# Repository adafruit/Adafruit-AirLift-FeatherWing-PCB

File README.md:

# Adafruit-AirLift-FeatherWing-PCB
PCB files for Adafruit AirLift FeatherWing

Format is EagleCAD schematic and board layout

For more details, check out the product page at

   * https://www.adafruit.com/product/4264

Adafruit invests time and resources providing this open source design, 
please support Adafruit and open-source hardware by purchasing 
products from Adafruit!

Designed by Adafruit Industries.  
Creative Commons Attribution, Share-Alike license, check license.txt for more information
All text above must be included in any redistribution

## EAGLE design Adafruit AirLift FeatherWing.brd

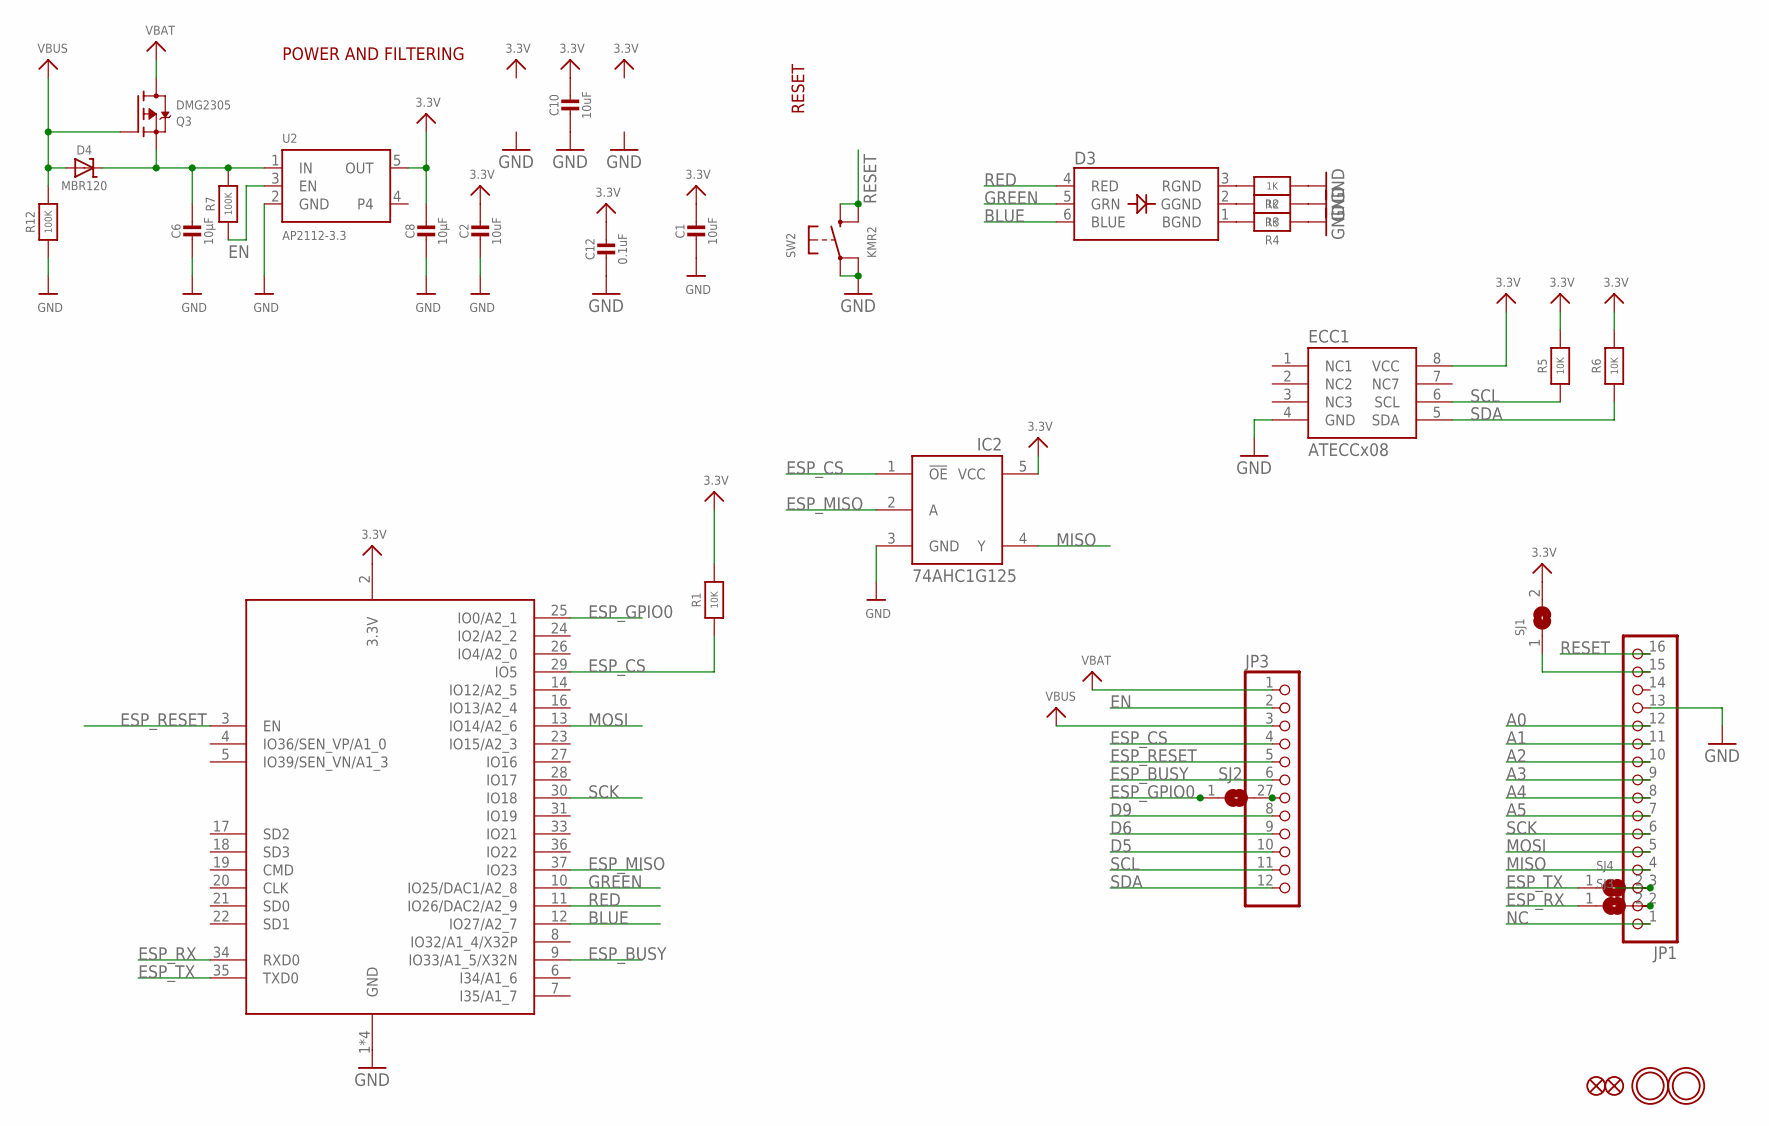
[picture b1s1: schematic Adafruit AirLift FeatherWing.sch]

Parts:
C1, C2, C10: 10uF; 0805-NO
C6, C8: 10µF; 0805-NO
C12: 0.1uF; 0603-NO
D3: LED_RGB_PLCC6CREE-CLV6A; RGBLED_PLCC6
D4: MBR120; SOD-123
ECC1: ATECCx08; SOIC8
IC2: 74AHC1G125; SOT23-5L
JP1: HEADER-1X16_MIN; 1X16_ROUND_MIN
JP3: HEADER-1X12_MIN; 1X12_ROUND_MIN
Q3: DMG2305; SOT23-R
R1, R5, R6: 10K; 0603-NO
R2, R3, R4: 1K; 0603-NO
R7, R12: 100K; 0603-NO
SJ1, SJ2, SJ3, SJ4: SOLDERJUMPER; SOLDERJUMPER_ARROW_NOPASTE
SW2: KMR2; BTN_KMR2_4.6X2.8
U2: AP2112-3.3; SOT23-5
U$31, U$32: MOUNTINGHOLE2.5; MOUNTINGHOLE_2.5_PLATED
U$34, U$35: FIDUCIAL_1MM
X3: ESP32_WROOM32_SKINNY; WROOM32_SKINNY

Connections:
3.3V: C1.1, C2.1, C8.1, C10.1, C12.1, ECC1.8 (VCC), IC2.5 (VCC), R1.2, R5.2, R6.2, SJ1.2, U2.5 (OUT), X3.2 (3.3V)
A0: JP1.12
A1: JP1.11
A2: JP1.10
A3: JP1.9
A4: JP1.8
A5: JP1.7
BLUE: D3.6 (BLUE), X3.12 (IO27/A2_7)
D5: JP3.10
D6: JP3.9
D9: JP3.8
EN: JP3.2, R7.1, U2.3 (EN)
ESP_BUSY: JP3.6, X3.9 (IO33/A1_5/X32N)
ESP_CS: IC2.1 (!OE), JP3.4, R1.1, X3.29 (IO5)
ESP_GPIO0: SJ2.1, X3.25 (IO0/A2_1)
ESP_MISO: IC2.2 (A), X3.37 (IO23)
ESP_RESET: JP3.5, X3.3 (EN)
ESP_RX: SJ3.1, X3.34 (RXD0)
ESP_TX: SJ4.1, X3.35 (TXD0)
GND: C1.2, C2.2, C6.2, C8.2, C10.2, C12.2, ECC1.4 (GND), IC2.3 (GND), JP1.13, R2.1, R3.1, R4.1, R12.1, SW2.A, SW2.A' (P1), U2.2 (GND), X3.1 (GND), X3.15 (GND), X3.38 (GND), X3.P$1 (GND)
GREEN: D3.5 (GRN), X3.10 (IO25/DAC1/A2_8)
MISO: IC2.4 (Y), JP1.4
MOSI: JP1.5, X3.13 (IO14/A2_6)
unnamed: JP1.15, SJ1.1
unnamed: D3.3 (RGND), R2.2
unnamed: D3.2 (GGND), R3.2
unnamed: D3.1 (BGND), R4.2
unnamed: JP3.7, SJ2.2
unnamed: JP1.2, SJ3.2
unnamed: C6.1, D4.C, Q3.2 (S), R7.2, U2.1 (IN)
unnamed: JP1.3, SJ4.2
NC: JP1.1
RED: D3.4 (RED), X3.11 (IO26/DAC2/A2_9)
RESET: JP1.16, SW2.B (S), SW2.B' (S1)
SCK: JP1.6, X3.30 (IO18)
SCL: ECC1.6 (SCL), JP3.11, R5.1
SDA: ECC1.5 (SDA), JP3.12, R6.1
VBAT: JP3.1, Q3.3 (D)
VBUS: D4.A, JP3.3, Q3.1 (G), R12.2

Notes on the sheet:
POWER AND FILTERING
RESET

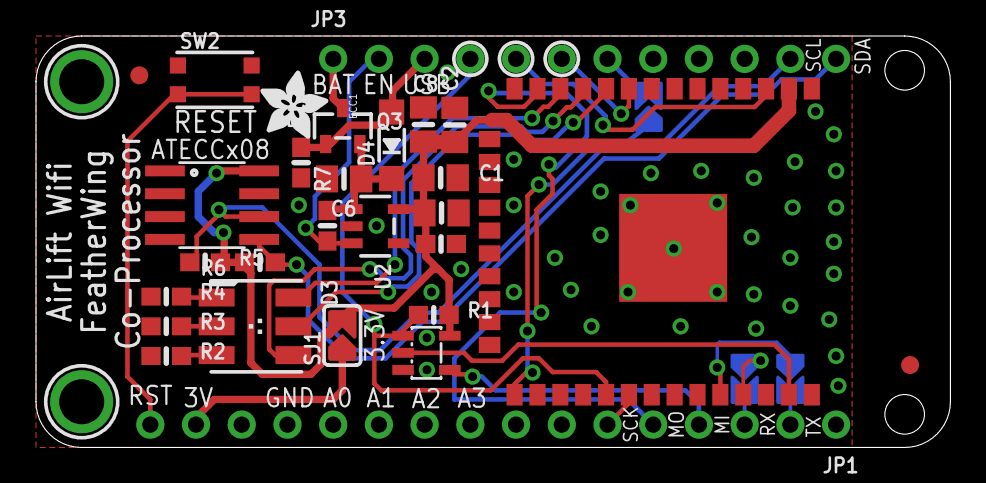
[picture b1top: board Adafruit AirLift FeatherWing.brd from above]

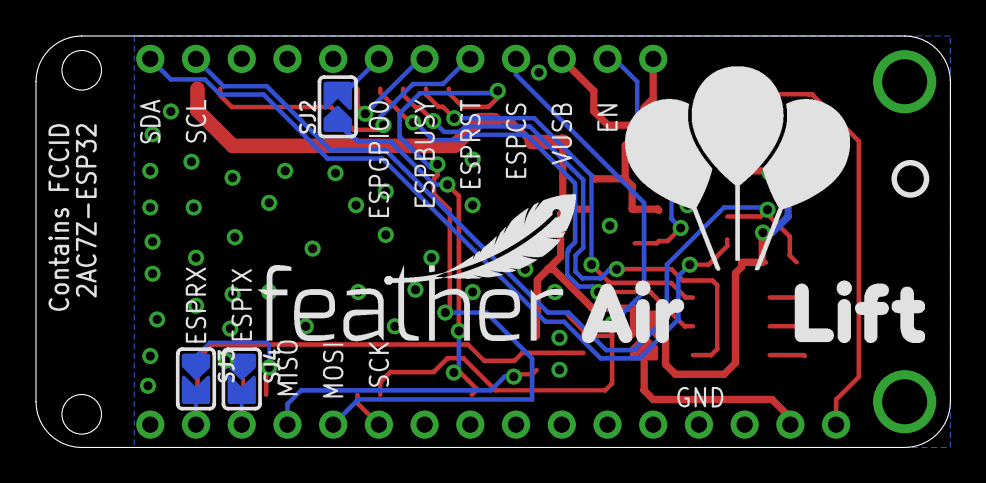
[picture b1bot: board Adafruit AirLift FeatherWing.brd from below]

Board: 2 copper layers, 50.8 x 22.9 mm, 36 parts (6 on the bottom side), 29 nets.

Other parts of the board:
U$6: AIRLIFT
U$7: FEATHERLOGO_MED
U$13: PCBFEAT-REV-040
U$15: ADAFRUIT_3.5MM

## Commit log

2019-05-29 Adding board files

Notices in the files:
parts and their libraries:
microbuilder: This work is placed in the public domain, and may be freely used for commercial and non-commercial work with the following conditions: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
SparkFun-Aesthetics: Licensing: CC v3.0 Share-Alike You are welcome to use this library for commercial purposes.
